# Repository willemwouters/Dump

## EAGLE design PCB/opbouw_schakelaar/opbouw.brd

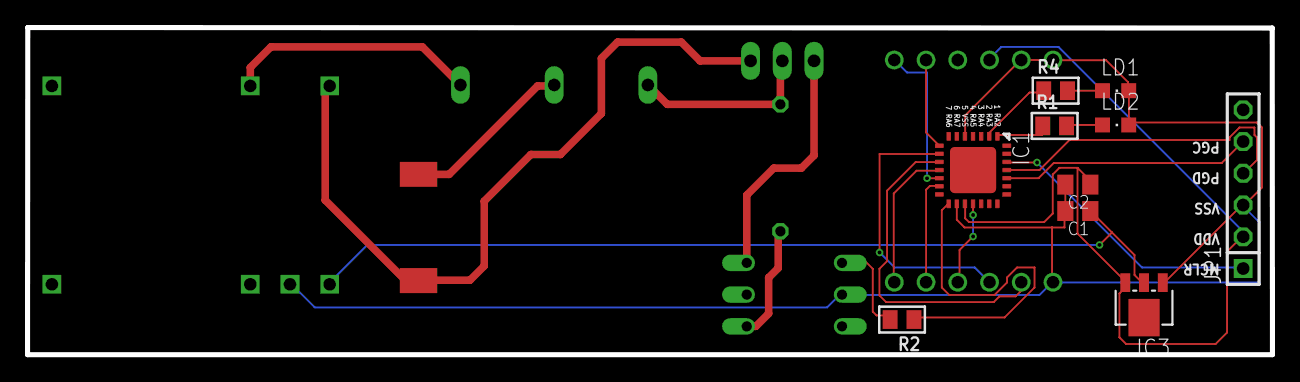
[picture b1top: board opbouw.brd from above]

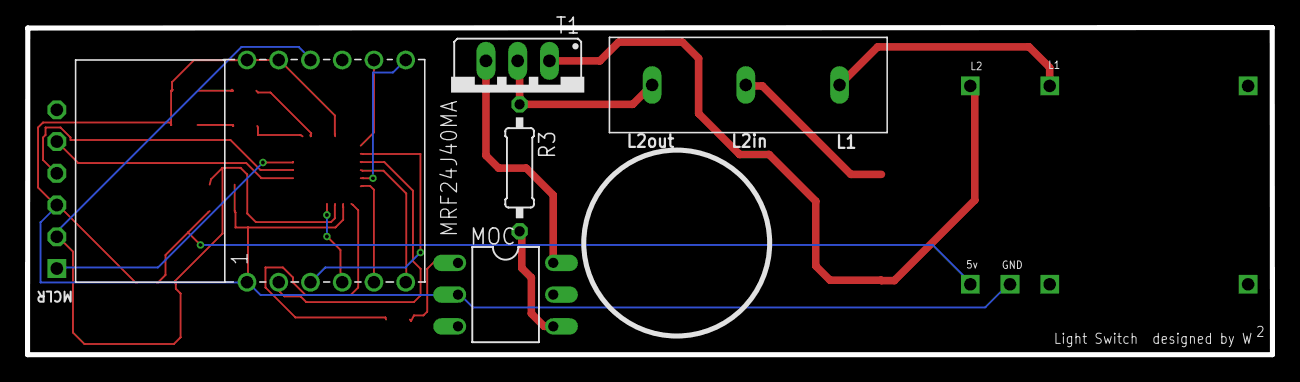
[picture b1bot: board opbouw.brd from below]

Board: 2 copper layers, 99.6 x 26.2 mm, 17 parts (5 on the bottom side), 25 nets.

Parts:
C1, C2: C0805K
IC1: PIC24FJ16GA002_QFN; QFN28-ML_6X6MM
IC3: S-812XSGUP; SOT89
JP1: 1X06
LD1, LD2: CHIPLED_0805
MOC: 4N33; DIL06
R1, R2, R4: R0805
R3: 0207/10
T1: TIC126; TO220CS
U$1: MRF24J40MA
U$2: CONNECTOR
U$3: FUSEFUSE; FUSE
U$4: BIAS

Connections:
unnamed: C2.1, IC1.17, IC3.3, JP1.2, U$1.VIN
unnamed: IC1.26, JP1.1
unnamed: IC1.25, JP1.4
unnamed: IC1.24, JP1.5
unnamed: IC1.8, U$1.CS(LOW)
unnamed: IC1.15, R2.1
unnamed: IC1.10, U$1.RESET
unnamed: IC1.13, U$1.SDI
unnamed: IC1.18, U$1.INT
unnamed: IC1.9, U$1.WAKE
unnamed: IC1.11, U$1.SCK
unnamed: MOC.6, T1.G
unnamed: MOC.1, R2.2
unnamed: IC1.12, U$1.SDO
unnamed: MOC.4, R3.2
unnamed: U$2.P$2, U$3.P$1
unnamed: R3.1, T1.A, U$2.P$3
unnamed: IC1.1, R1.1
unnamed: IC1.2, R4.1
unnamed: LD2.A, R1.2
unnamed: LD1.A, R4.2
unnamed: C1.2, C2.2, IC1.5, IC1.16, IC3.1, JP1.3, LD1.C, LD2.C, MOC.2, U$1.GND, U$1.GND1, U$1.GND2, U$4.P$4
unnamed: C1.1, IC3.2, U$4.P$3
unnamed: T1.C, U$3.P$2, U$4.P$1
unnamed: U$2.P$1, U$4.P$2

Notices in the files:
parts and their libraries:
rc-master: Copyright (C) 2007, Bob Starr
